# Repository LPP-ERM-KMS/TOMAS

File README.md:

# TOMAS
This repository will contain all the files relevant for the operation of TOMAS

## DataAnalysis
A program to analyse DAQ data

https://github.com/LPP-ERM-KMS/TOMAS/assets/66306556/d6c48096-511a-469a-aade-b6a6144d4a86

## TOMAS-main
This is the software that drives the main computer 

## ToF-NPA
Files relevant to the time of flight neutral particle analyser, most notably this contains software to analyze the data.

## Calibrations
Data on all kinds of calibrations performed on TOMAS

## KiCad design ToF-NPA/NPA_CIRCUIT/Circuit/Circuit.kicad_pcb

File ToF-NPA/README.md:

# ToF-NPA

## NPA Code

This is software capable of analysing compass raw csv datafiles, just run the file *NPA_DataAnalysis_v4.py*

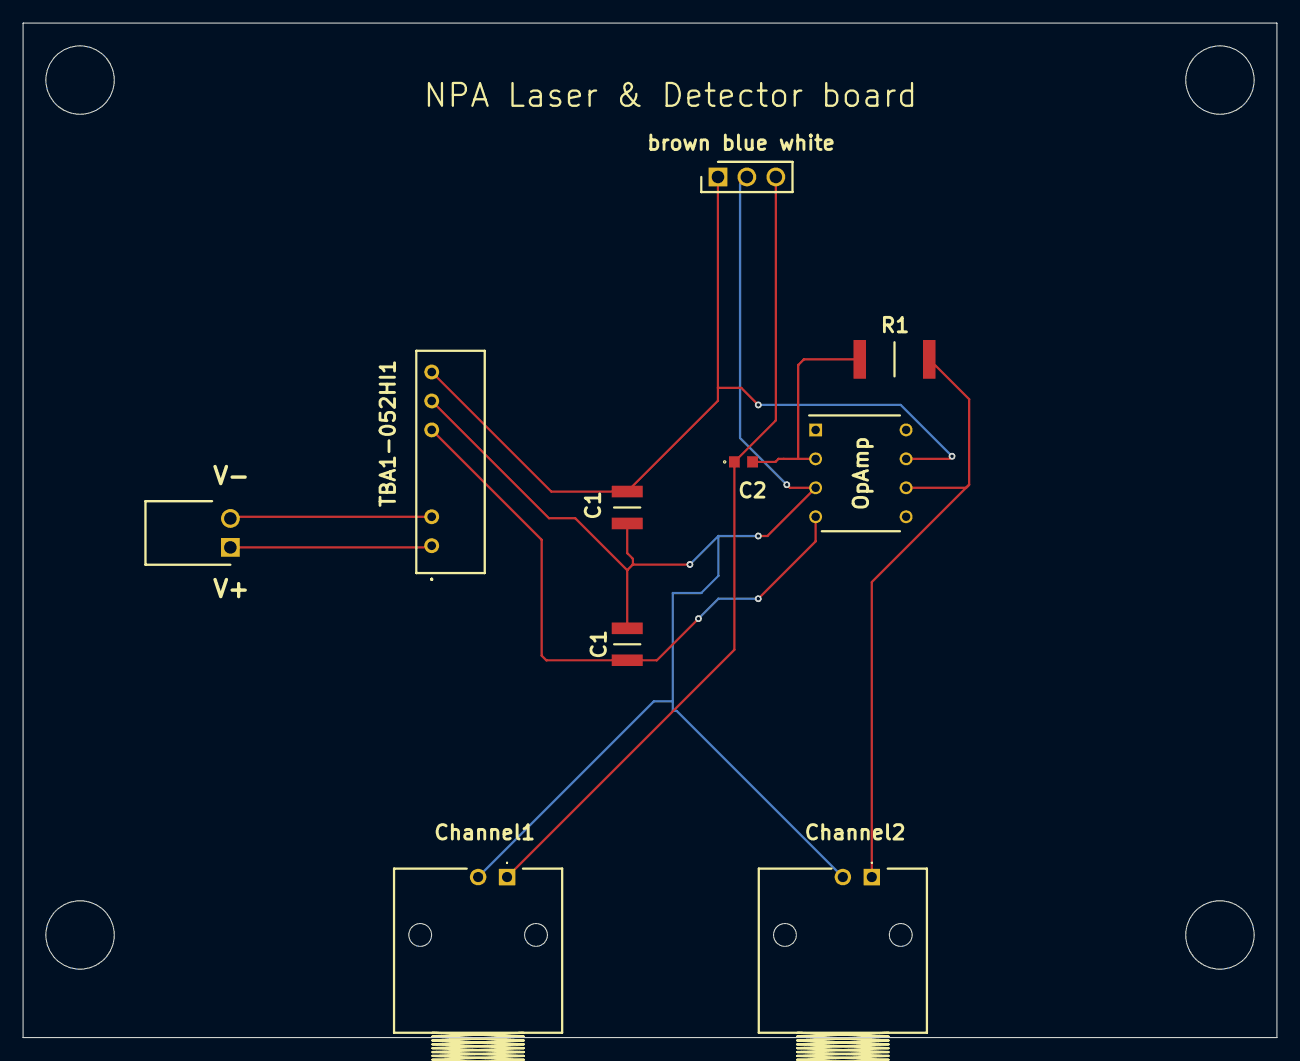
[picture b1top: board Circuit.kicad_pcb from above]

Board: 2 copper layers, 110.0 x 89.0 mm, 10 parts (0 on the bottom side), 8 nets.

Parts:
C1, C1#2: 12103C106K4Z2A; CAPC3225X279N
C2: C0603H470J5GACTU; C0603
Channel1, Channel2: CONBNC002
J1: BG302-02-A-L-G; RHDRRA2W64P0X254_1X2_558X570X265P
OpAmp: LT1115CN8#PBF; DIP794W53P254L1016H394Q8N
R1: CRGP2512F1M0; RESC6432X65N
TBA1-052HI1: TBA_1-0521HI; TBA10521HI
brown blue white: BG030-03-A-0450-0300-N-G; HDRV3W64P0X254_1X3_762X250X724P

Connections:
+5V: C1.1, OpAmp.7 (V+), TBA1-052HI1.7 (_+VOUT), brown blue white.1
-5V: C1#2.2, OpAmp.4 (V-), TBA1-052HI1.5 (-VOUT)
GND: C1.2, C1#2.1, Channel1.2, Channel2.2, OpAmp.3 (+IN), TBA1-052HI1.6 (COMMON), brown blue white.2
unnamed: C2.1, Channel1.1, brown blue white.3
unnamed: C2.2, OpAmp.2 (-IN), R1.1
unnamed: Channel2.1, OpAmp.6 (OUT), R1.2
unnamed: J1.2, TBA1-052HI1.2 (-VIN_(GND))
unnamed: J1.1, TBA1-052HI1.1 (_+VIN_(VCC)_)

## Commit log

2023-10-11 added main operation software
2023-10-11 created the relevant folders
2023-10-12 should be implemented
2023-10-31 added sim code
2023-10-31 added info on ToF file
2023-11-13 updated main
2023-11-13 so the low EC power end is fitted, and threading was implemented to make the program not freeze when moving the probes
2023-11-24 writing Nelder-Mead matching software
2023-11-27 made the basic semi-automatic gui, only problem remaining: displaying suggested capacitor values
2023-11-27 semi-automatic matching system is donegit add .! Well I guess some abort button is still necesarry
2023-11-29 should be about done now, now just need to fire up a simulation for all possible freqs but will do that tomorrow
2023-11-30 simulated a bunch more data
2023-12-12 made the Capacitors more accurate
2023-12-12 first attempt at matching system
2023-12-12 only MOVE button doesn't work
2023-12-20 added DAQ control software and updated main
2023-12-20 hopefully this is the fix
2024-01-10 I don't remember what changed
2024-01-17 creating sputtering calculations code
2024-01-24 done with making sputtering approx
2024-01-24 ok now we're done
2024-02-13 some software updates
2024-02-19 Creating Data analysis software
2024-02-20 Made it possible to convert signals to calibrated correspondence
2024-02-20 trying to embed video in readme
2024-02-20 added video to readme
2024-02-20 better wording and mention of software in main readme
2024-02-20 better demo
2024-02-20 Better readability
2024-02-20 less aggression
2024-02-20 gave windows a little seperate header
2024-02-20 suggestions update
2024-02-20 little grammar update
2024-02-20 better framing
2024-02-20 working on export possibility
2024-02-21 now able to convert folder to other file formats
2024-02-21 ok csv is kinda slow but it'll manage
2024-02-21 added new tutorial
2024-02-21 changed video encoding as github had some issues
2024-02-26 calibration of penning and baratron updated
2024-02-27 Added video to foremost readme
2024-03-06 Probs won't work perfectly when actually installing but will get us there
2024-03-06 move to main
2024-03-08 added ability to view TP scan
2024-03-08 added direction choice
2024-03-08 quitting for now
2024-03-12 Trying to predict passing probabilities
2024-03-12 almost done with the setup part
2024-03-12 fixed
2024-03-12 Now also supports TP_ naming scheme
2024-03-12 Better tutorial
2024-03-12 error in density calculation fixed
2024-03-12 okaaay letsgo
2024-03-12 cleanup
2024-03-13 doing calibrations
2024-03-13 added S-matrices
2024-03-13 newest DAQ software upload
2024-03-13 re-measured as one file was corrupted
2024-03-13 smaller ICCalibration file, such that clone is faster
2024-03-18 updated PlotData and the GUI matching
2024-03-19 calibration update
2024-03-19 finished circuit calibration now just have to implement in GUI
2024-03-20 gui implemented
2024-03-21 building pcb
2024-03-22 circuit is done
2024-03-22 made coax easier to put in box
2024-03-22 changed resistor to 2W rating
2024-03-22 was wired wrong, happely catched it just in time
2024-03-22 now we're done
2024-03-27 report and circuit update
2024-03-28 small update
2024-03-28 small bug
2024-03-28 Added injected power graph
2024-04-08 better fitting
2024-04-12 shouldn't upload figures
2024-04-12 added EC manual
2024-04-16 Now using numpy computations, it is thus 100x faster
2024-04-16 further optimisation
2024-04-16 added bunch of sliders
2024-04-16 bigger slider
2024-04-17 new parameters
2024-04-18 forgot to change something small
2024-04-18 works now
2024-04-19 Phase calibration is done
2024-04-19 need to update this even more at some point..
2024-04-23 TOMAS-main is how it's currently installed on the control pc
2024-04-23 Added phase cal in software
2024-04-24 Big update: new fitting method + significant digits
2024-04-25 perfection
2024-04-26 added spectrometer manual
2024-05-07 matching algorithm system in place
2024-05-08 did some matching
2024-05-21 3s should suffice
2024-07-03 added way of estimating ion erosion
2024-07-03 damn
2024-08-27 now up to date with installed firmware
2024-08-29 distance doesn't quite seem to work good yet
2024-09-04 working on the IC modeling
2024-09-09 further modeling done
2024-09-10 not for the public eye jet 😉 (not that it matters actually)
2024-11-14 writing the manual
2024-11-18 case now with step of circuit
2024-11-18 motor wiring done, now diagnostics
2024-11-19 updating diagnostics
2024-11-26 now with .0mm accuracy ;)
2024-11-28 should've made it possible to communicate switches to arduino
2024-11-28 implemented into python code :)
2024-11-28 done! works :)
2024-12-02 1st Draft
    1st Draft
2024-12-02 implemented saving of parameters
2024-12-02 logboek toegevoegd
2024-12-02 re-wrote relative file loc
2024-12-02 made resilient to weird inputs
2024-12-02 small mistake
2024-12-02 Draft 0.1
2024-12-03 small changes, dotfiles are annoying tho
2024-12-03 smol mistake
2024-12-04 added some manuals
2024-12-04 when did this change wtf
2024-12-10 adapted version
2024-12-10 new update
2024-12-11 TOMAS-main updates
2024-12-11 ignore weird files
2024-12-20 Added quadrupole probe calculation
2024-12-20 updated GUI and DAQ
2025-01-14 reduced and deleted unecessary images, also arduino firmware should ideally not be touched
2025-01-14 added smoothing option
2025-01-16 fixed smoothing
2025-01-29 added (broken at time of writing) IC amp manual
2025-01-31 calibrated GD voltage divider at anode
2025-02-07 update Glow discharge
